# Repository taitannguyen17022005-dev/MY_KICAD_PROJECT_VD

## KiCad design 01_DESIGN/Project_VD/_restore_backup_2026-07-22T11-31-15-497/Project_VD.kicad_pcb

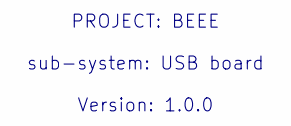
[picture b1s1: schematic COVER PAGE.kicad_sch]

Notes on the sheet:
PROJECT: BEEE sub-system: USB board Version: 1.0.0

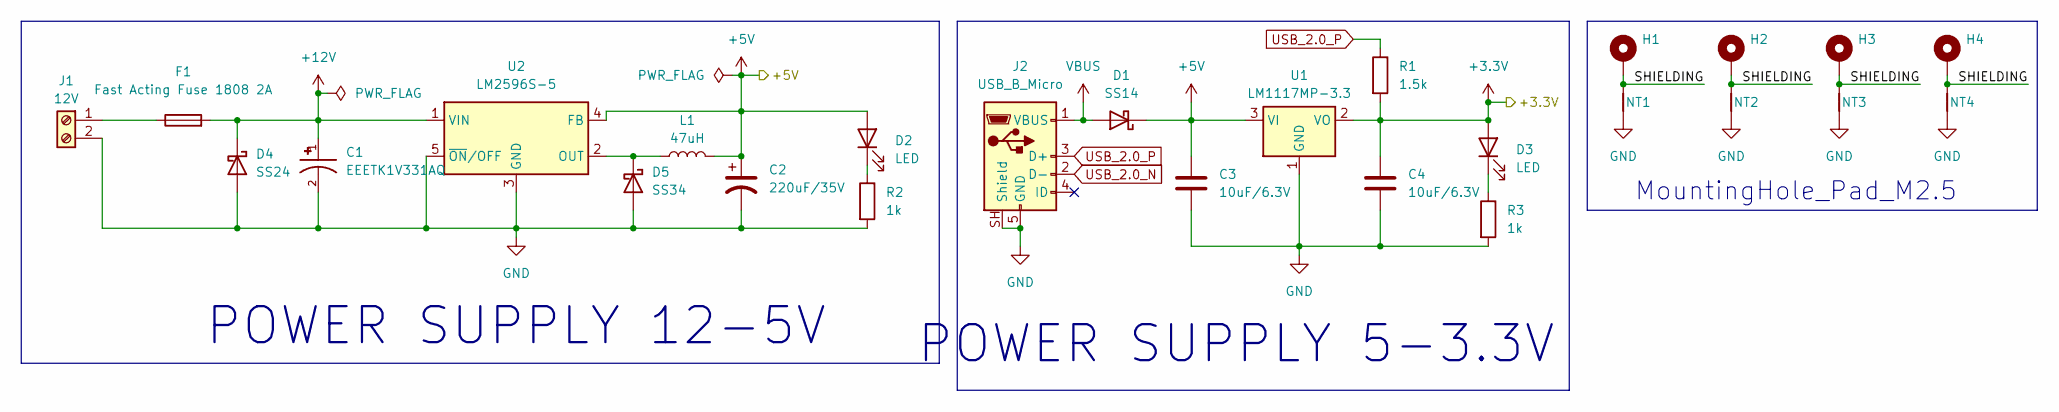
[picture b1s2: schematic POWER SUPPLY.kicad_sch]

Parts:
C1: EEETK1V331AQ; CAP_EEETK1V331AQ; PARTREV 10-Oct-19
C2: 220uF/35V; CP_Elec_8x10
C3, C4: 10uF/6.3V; C_0603_1608Metric
D1: SS14; D_SMA
D2, D3: LED; LED_0603_1608Metric
D4: SS24; D_SMA
D5: SS34; D_SMA
F1: Fast Acting Fuse 1808 2A; C_1808_4520Metric
H1, H2, H3, H4: MountingHole_Pad; MountingHole_2.7mm_M2.5_Pad
J1: 12V; TerminalBlock_Phoenix_PT-1,5-2-5.0-H_1x02_P5.00mm_Horizontal
J2: USB_B_Micro; USB_Micro-B_Molex_47346-0001
L1: 47uH; L_12x12mm_H8mm
NT1, NT2, NT3, NT4: NetTie_2; NetTie-2_SMD_Pad0.5mm
R1: 1.5k; R_0603_1608Metric
R2, R3: 1k; R_0603_1608Metric
U1: LM1117MP-3.3; SOT-223-3_TabPin2
U2: LM2596S-5; TO-263-5_TabPin3

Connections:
+3.3V: C4.1, D3.2 (A), R1.2, U1.2 (VO); also elsewhere on the board
+5V: C2.1, C3.1, D1.1 (K), D2.2 (A), L1.2, U1.3 (VI), U2.4 (FB); also elsewhere on the board
+12V: C1.1, D4.1 (K), F1.2, U2.1 (VIN)
/POWER 12 - 5V & 5 - 3.3V/SHIELDING: H1.1 (1_1), H2.1 (1_1), H3.1 (1_1), H4.1 (1_1), NT1.2, NT2.2, NT3.2, NT4.2
GND: C1.2, C2.2, C3.2, C4.2, D4.2 (A), D5.2 (A), J1.2, J2.5 (GND), J2.SH (Shield), NT1.1, NT2.1, NT3.1, NT4.1, R2.2, R3.2, U1.1 (GND), U2.3 (GND), U2.5 (~ON/OFF); also elsewhere on the board
unnamed: D2.1 (K), R2.1
unnamed: D3.1 (K), R3.1
unnamed: D5.1 (K), L1.1, U2.2 (OUT)
unnamed: F1.1, J1.1
USB_2.0_N: J2.2 (D-); also elsewhere on the board
USB_2.0_P: J2.3 (D+), R1.1; also elsewhere on the board
VBUS: D1.2 (A), J2.1 (VBUS)

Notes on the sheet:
POWER SUPPLY 12-5V
MountingHole_Pad_M2.5
POWER SUPPLY 5-3.3V

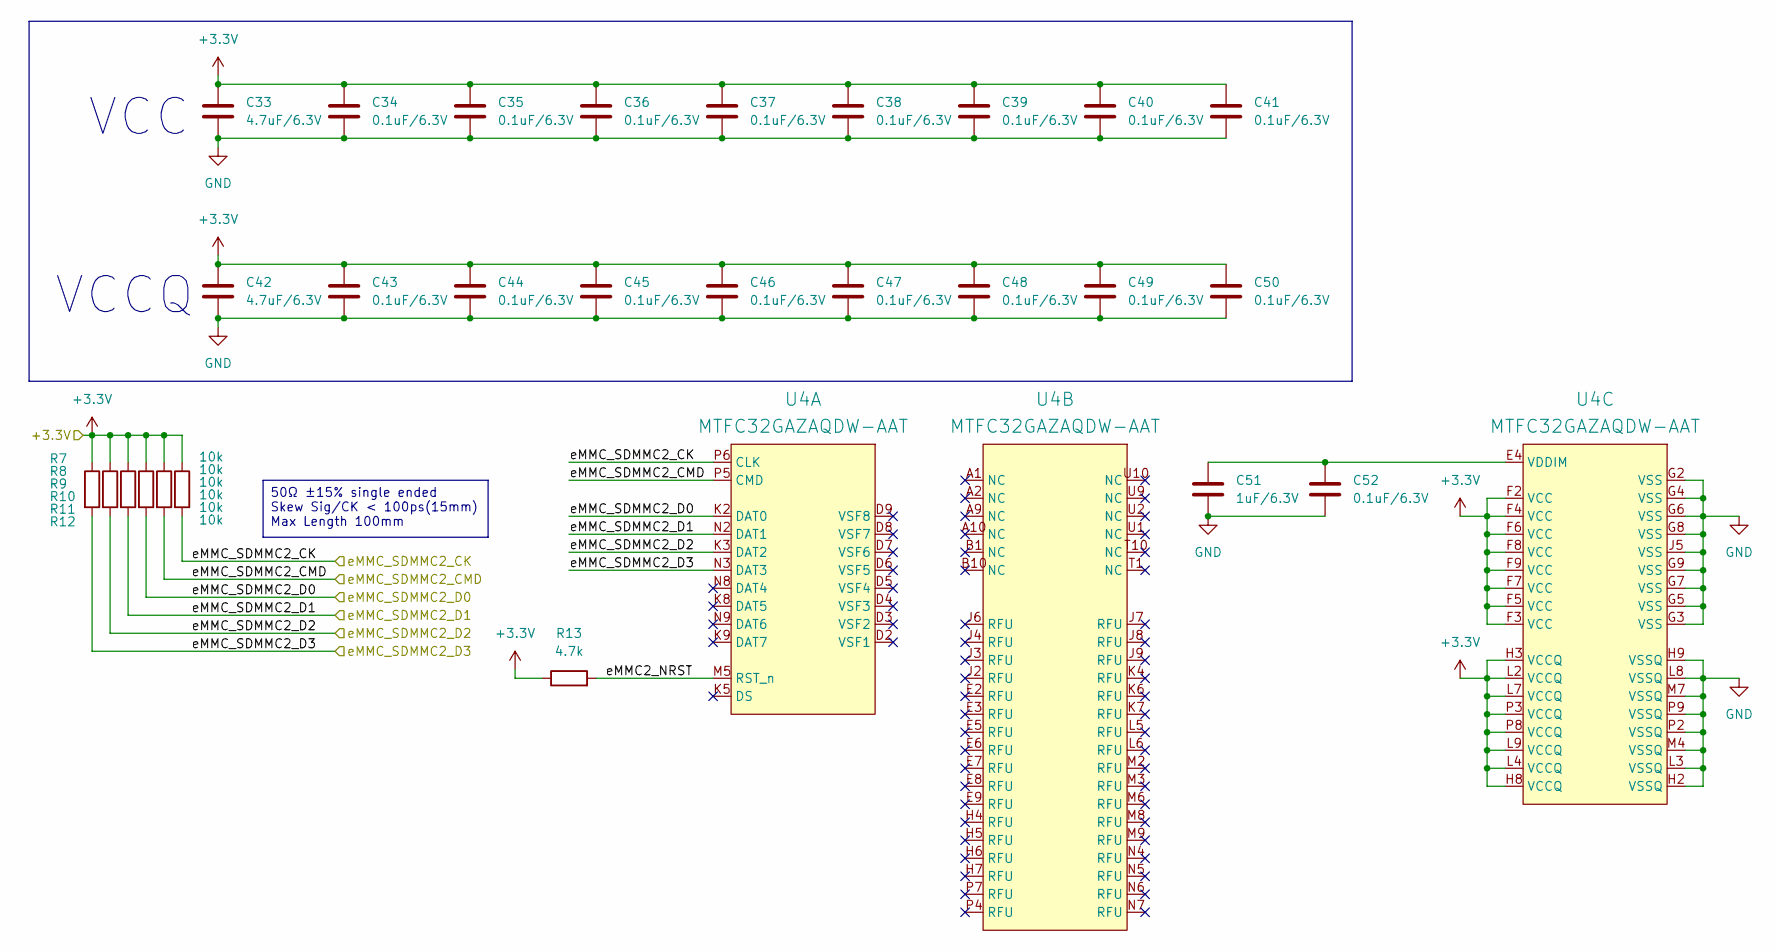
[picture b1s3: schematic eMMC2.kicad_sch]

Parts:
C33, C42: 4.7uF/6.3V; C_0603_1608Metric
C34, C35, C36, C37, C38, C39, C40, C41, C43, C44, C45, C46, C47, C48, C49, C50, C52: 0.1uF/6.3V; C_0603_1608Metric
C51: 1uF/6.3V; C_0603_1608Metric
R7, R8, R9, R10, R11, R12: 10k; C_0603_1608Metric
R13: 4.7k; C_0603_1608Metric
U4: MTFC32GAZAQDW-AAT; BGA-100_14x18mm_Layout10x17_P1mm

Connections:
+3.3V: C33.1, C34.1, C35.1, C36.1, C37.1, C38.1, C39.1, C40.1, C41.1, C42.1, C43.1, C44.1, C45.1, C46.1, C47.1, C48.1, C49.1, C50.1, R7.1, R8.1, R9.1, R10.1, R11.1, R12.1, R13.1, U4.F2 (VCC), U4.F3 (VCC), U4.F4 (VCC), U4.F5 (VCC), U4.F6 (VCC), U4.F7 (VCC), U4.F8 (VCC), U4.F9 (VCC), U4.H3 (VCCQ), U4.H8 (VCCQ), U4.L2 (VCCQ), U4.L4 (VCCQ), U4.L7 (VCCQ), U4.L9 (VCCQ), U4.P3 (VCCQ), U4.P8 (VCCQ); also elsewhere on the board
/eMMC2/eMMC2_NRST: R13.2, U4.M5 (RST_n)
/eMMC2/eMMC_SDMMC2_CK: R12.2, U4.P6 (CLK); also elsewhere on the board
/eMMC2/eMMC_SDMMC2_CMD: R11.2, U4.P5 (CMD); also elsewhere on the board
/eMMC2/eMMC_SDMMC2_D0: R10.2, U4.K2 (DAT0); also elsewhere on the board
/eMMC2/eMMC_SDMMC2_D1: R9.2, U4.N2 (DAT1); also elsewhere on the board
/eMMC2/eMMC_SDMMC2_D2: R8.2, U4.K3 (DAT2); also elsewhere on the board
/eMMC2/eMMC_SDMMC2_D3: R7.2, U4.N3 (DAT3); also elsewhere on the board
GND: C33.2, C34.2, C35.2, C36.2, C37.2, C38.2, C39.2, C40.2, C41.2, C42.2, C43.2, C44.2, C45.2, C46.2, C47.2, C48.2, C49.2, C50.2, C51.2, C52.2, U4.G2 (VSS), U4.G3 (VSS), U4.G4 (VSS), U4.G5 (VSS), U4.G6 (VSS), U4.G7 (VSS), U4.G8 (VSS), U4.G9 (VSS), U4.H2 (VSSQ), U4.H9 (VSSQ), U4.J5 (VSS), U4.L3 (VSSQ), U4.L8 (VSSQ), U4.M4 (VSSQ), U4.M7 (VSSQ), U4.P2 (VSSQ), U4.P9 (VSSQ); also elsewhere on the board
unnamed: C51.1, C52.1, U4.E4 (VDDIM)

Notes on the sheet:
VCC
VCCQ
50Ω ±15% single ended Skew Sig/CK < 100ps(15mm) Max Length 100mm

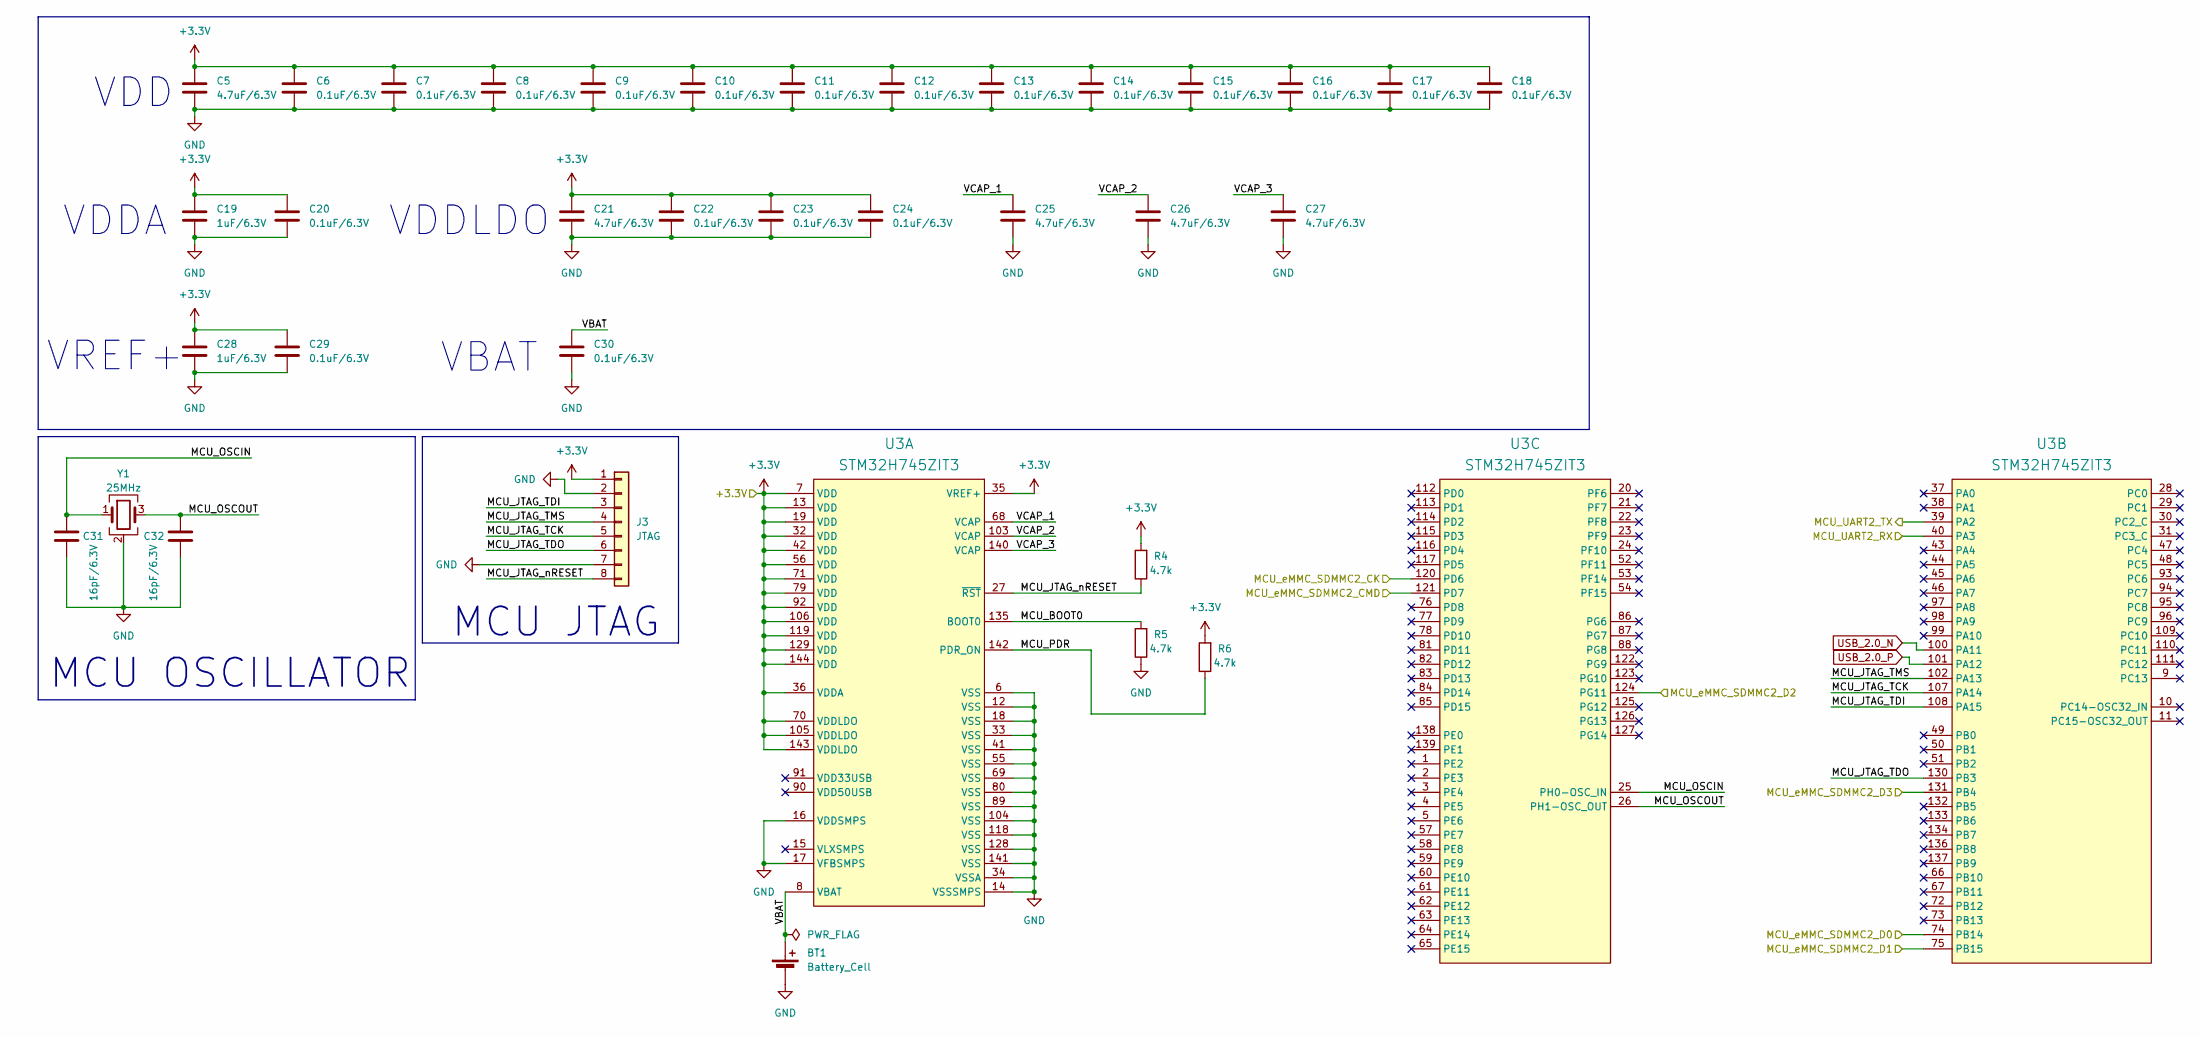
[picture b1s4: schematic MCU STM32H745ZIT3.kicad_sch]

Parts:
BT1: Battery_Cell; BatteryHolder_Keystone_1060_1x2032
C5, C21, C25, C26, C27: 4.7uF/6.3V; C_0603_1608Metric
C6, C7, C8, C9, C10, C11, C12, C13, C14, C15, C16, C17, C18, C20, C22, C23, C24, C29, C30: 0.1uF/6.3V; C_0603_1608Metric
C19, C28: 1uF/6.3V; C_0603_1608Metric
C31, C32: 16pF/6.3V; C_0603_1608Metric
J3: JTAG; PinHeader_1x08_P2.54mm_Vertical
R4, R5, R6: 4.7k; C_0603_1608Metric
U3: STM32H745ZIT3; LQFP-144_20x20mm_P0.5mm; Manufacturer Part Number STM32H745ZIT6; Digikey Description HIGH-PERFORMANCE AND DSP WITH DP
Y1: 25MHz; Crystal_SMD_3225-4Pin_3.2x2.5mm

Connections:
+3.3V: C5.1, C6.1, C7.1, C8.1, C9.1, C10.1, C11.1, C12.1, C13.1, C14.1, C15.1, C16.1, C17.1, C18.1, C19.1, C20.1, C21.1, C22.1, C23.1, C24.1, C28.1, C29.1, J3.1, R4.2, R6.2, U3.7 (VDD), U3.13 (VDD), U3.19 (VDD), U3.32 (VDD), U3.35 (VREF+), U3.36 (VDDA), U3.42 (VDD), U3.56 (VDD), U3.70 (VDDLDO), U3.71 (VDD), U3.79 (VDD), U3.92 (VDD), U3.105 (VDDLDO), U3.106 (VDD), U3.119 (VDD), U3.129 (VDD), U3.143 (VDDLDO), U3.144 (VDD); also elsewhere on the board
/ISO_UART/ISO_UART2_RX: U3.40 (PA3); also elsewhere on the board
/ISO_UART/ISO_UART2_TX: U3.39 (PA2); also elsewhere on the board
/MCU STM32H745ZIT3/MCU_BOOT0: R5.2, U3.135 (BOOT0)
/MCU STM32H745ZIT3/MCU_JTAG_TCK: J3.5, U3.107 (PA14)
/MCU STM32H745ZIT3/MCU_JTAG_TDI: J3.3, U3.108 (PA15)
/MCU STM32H745ZIT3/MCU_JTAG_TDO: J3.6, U3.130 (PB3)
/MCU STM32H745ZIT3/MCU_JTAG_TMS: J3.4, U3.102 (PA13)
/MCU STM32H745ZIT3/MCU_JTAG_nRESET: J3.8, R4.1, U3.27 (~RST)
/MCU STM32H745ZIT3/MCU_OSCIN: C31.1, U3.25 (PH0-OSC_IN), Y1.1
/MCU STM32H745ZIT3/MCU_OSCOUT: C32.1, U3.26 (PH1-OSC_OUT), Y1.3
/MCU STM32H745ZIT3/MCU_PDR: R6.1, U3.142 (PDR_ON)
/MCU STM32H745ZIT3/VBAT: BT1.1 (+), C30.1, U3.8 (VBAT)
/MCU STM32H745ZIT3/VCAP_1: C25.1, U3.68 (VCAP)
/MCU STM32H745ZIT3/VCAP_2: C26.1, U3.103 (VCAP)
/MCU STM32H745ZIT3/VCAP_3: C27.1, U3.140 (VCAP)
/eMMC2/eMMC_SDMMC2_CK: U3.120 (PD6); also elsewhere on the board
/eMMC2/eMMC_SDMMC2_CMD: U3.121 (PD7); also elsewhere on the board
/eMMC2/eMMC_SDMMC2_D0: U3.74 (PB14); also elsewhere on the board
/eMMC2/eMMC_SDMMC2_D1: U3.75 (PB15); also elsewhere on the board
/eMMC2/eMMC_SDMMC2_D2: U3.124 (PG11); also elsewhere on the board
/eMMC2/eMMC_SDMMC2_D3: U3.131 (PB4); also elsewhere on the board
GND: BT1.2 (-), C5.2, C6.2, C7.2, C8.2, C9.2, C10.2, C11.2, C12.2, C13.2, C14.2, C15.2, C16.2, C17.2, C18.2, C19.2, C20.2, C21.2, C22.2, C23.2, C24.2, C25.2, C26.2, C27.2, C28.2, C29.2, C30.2, C31.2, C32.2, J3.2, J3.7, R5.1, U3.6 (VSS), U3.12 (VSS), U3.14 (VSSSMPS), U3.16 (VDDSMPS), U3.17 (VFBSMPS), U3.18 (VSS), U3.33 (VSS), U3.34 (VSSA), U3.41 (VSS), U3.55 (VSS), U3.69 (VSS), U3.80 (VSS), U3.89 (VSS), U3.104 (VSS), U3.118 (VSS), U3.128 (VSS), U3.141 (VSS), Y1.2 (G), Y1.4 (G); also elsewhere on the board
USB_2.0_N: U3.100 (PA11); also elsewhere on the board
USB_2.0_P: U3.101 (PA12); also elsewhere on the board

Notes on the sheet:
VDD
MCU JTAG
VREF+
MCU OSCILLATOR
VBAT
VDDLDO
VDDA

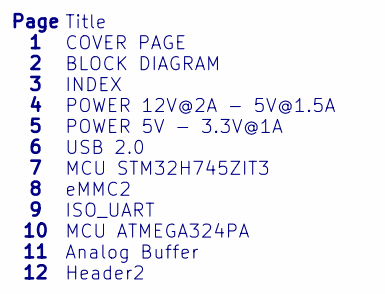
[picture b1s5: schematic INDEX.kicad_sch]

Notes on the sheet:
Page 1 2 3 4 5 6 7 8 9 10 11 12
Title COVER PAGE BLOCK DIAGRAM INDEX POWER 12V@2A - 5V@1.5A POWER 5V - 3.3V@1A USB 2.0 MCU STM32H745ZIT3 eMMC2 ISO_UART MCU ATMEGA324PA Analog Buffer Header2

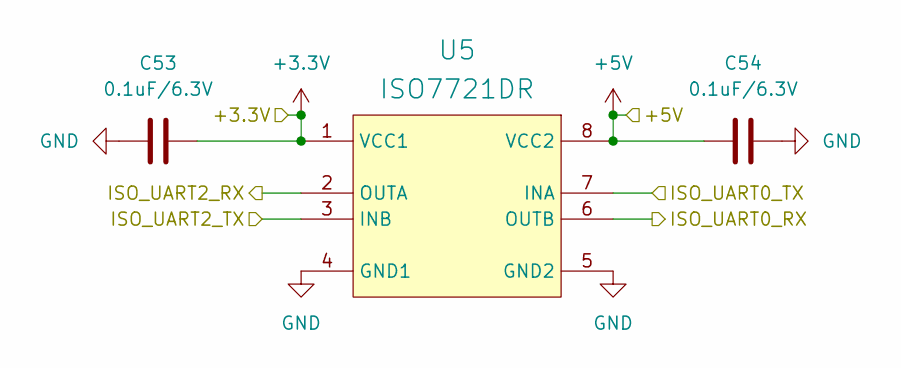
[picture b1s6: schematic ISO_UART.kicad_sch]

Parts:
C53, C54: 0.1uF/6.3V; C_0603_1608Metric
U5: ISO7721DR; SOIC-8_3.9x4.9mm_P1.27mm

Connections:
+3.3V: C53.2, U5.1 (VCC1); also elsewhere on the board
+5V: C54.2, U5.8 (VCC2); also elsewhere on the board
/ISO_UART/ISO_UART0_RX: U5.6 (OUTB); also elsewhere on the board
/ISO_UART/ISO_UART0_TX: U5.7 (INA); also elsewhere on the board
/ISO_UART/ISO_UART2_RX: U5.2 (OUTA); also elsewhere on the board
/ISO_UART/ISO_UART2_TX: U5.3 (INB); also elsewhere on the board
GND: C53.1, C54.1, U5.4 (GND1), U5.5 (GND2); also elsewhere on the board

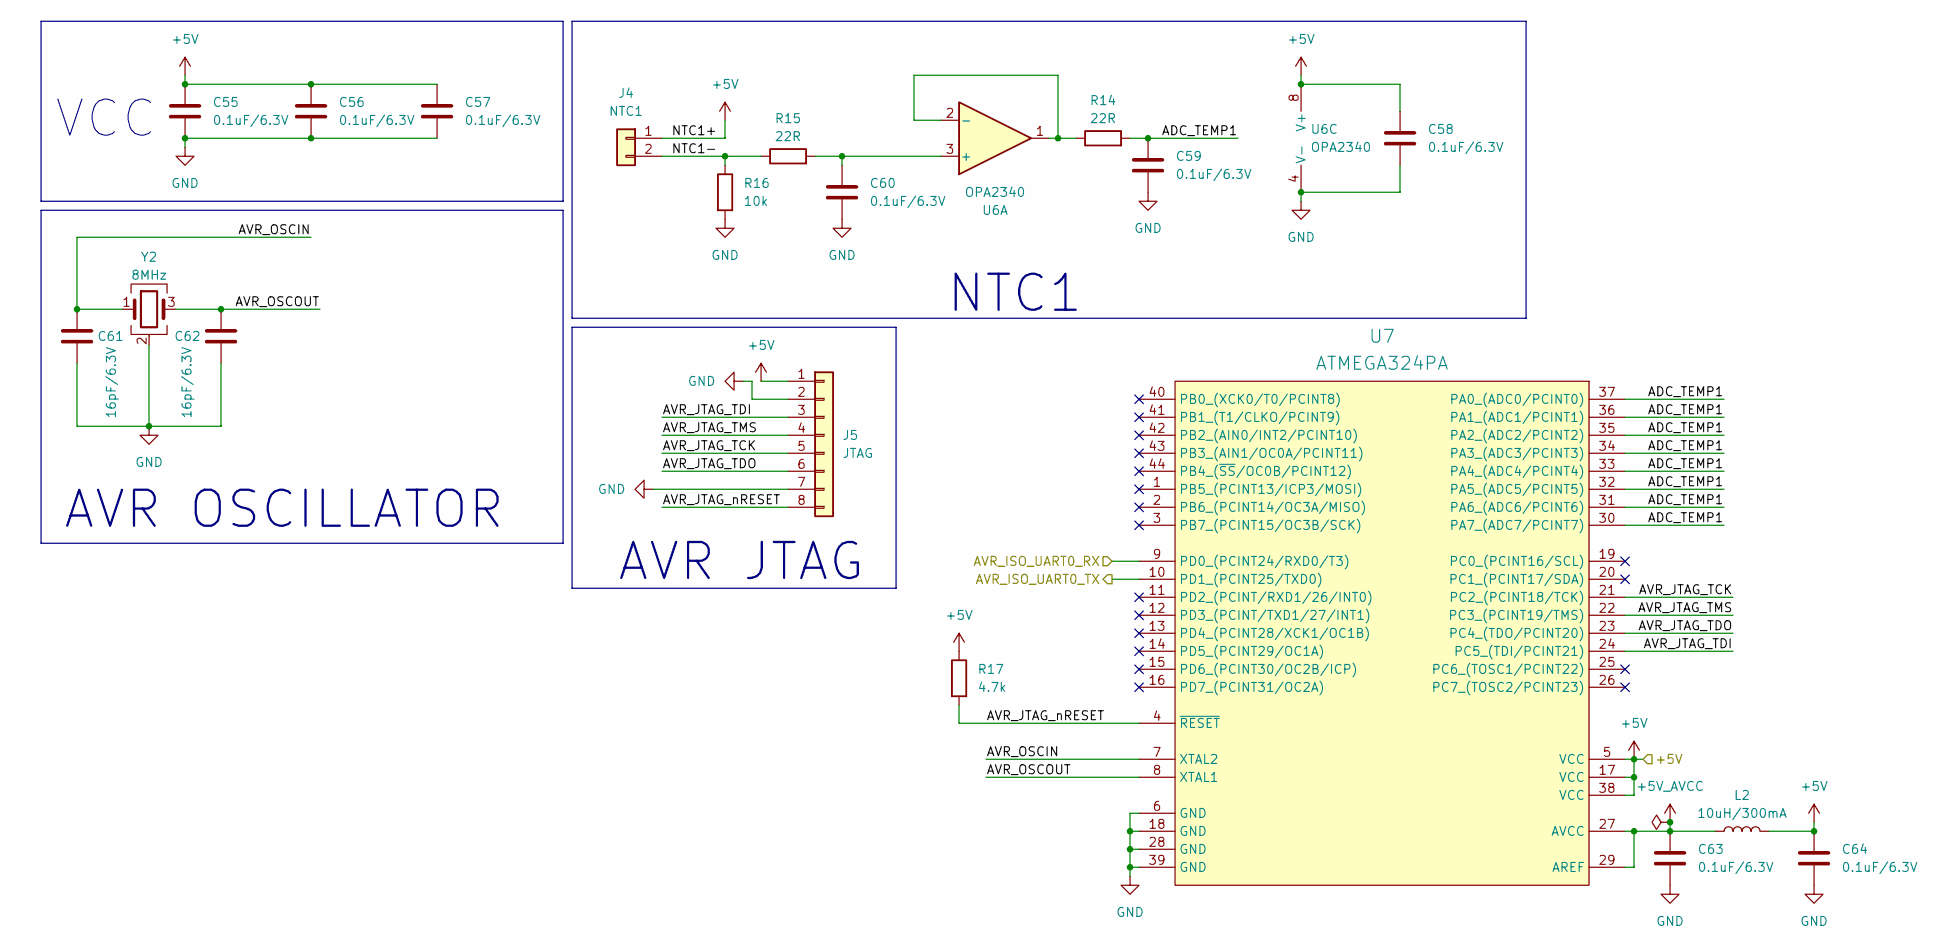
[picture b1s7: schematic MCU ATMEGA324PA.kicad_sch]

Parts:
C55, C56, C57, C58, C59, C60, C63, C64: 0.1uF/6.3V; C_0603_1608Metric
C61, C62: 16pF/6.3V; C_0603_1608Metric
J4: NTC1; PinHeader_1x02_P2.54mm_Vertical
J5: JTAG; PinHeader_1x08_P2.54mm_Vertical
L2: 10uH/300mA; L_0805_2012Metric
R14, R15: 22R; C_0603_1608Metric
R16: 10k; C_0603_1608Metric
R17: 4.7k; C_0603_1608Metric
U6: OPA2340; SOIC-8_3.9x4.9mm_P1.27mm
U7: ATMEGA324PA; TQFP-44_10x10mm_P0.8mm; Manufacturer Part Number ATMEGA324PA-AU
Y2: 8MHz; Crystal_SMD_3225-4Pin_3.2x2.5mm

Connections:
+5V: C55.1, C56.1, C57.1, C58.1, C64.1, J4.1, J5.1, L2.2, R17.1, U6.8 (V+), U7.5 (VCC), U7.17 (VCC), U7.38 (VCC); also elsewhere on the board
+5V_AVCC: C63.1, L2.1, U7.27 (AVCC), U7.29 (AREF)
/ISO_UART/ISO_UART0_RX: U7.9 (PD0_(PCINT24/RXD0/T3)); also elsewhere on the board
/ISO_UART/ISO_UART0_TX: U7.10 (PD1_(PCINT25/TXD0)); also elsewhere on the board
/MCU ATMEGA324PA/ADC_TEMP1: C59.1, R14.2, U7.30 (PA7_(ADC7/PCINT7)), U7.31 (PA6_(ADC6/PCINT6)), U7.32 (PA5_(ADC5/PCINT5)), U7.33 (PA4_(ADC4/PCINT4)), U7.34 (PA3_(ADC3/PCINT3)), U7.35 (PA2_(ADC2/PCINT2)), U7.36 (PA1_(ADC1/PCINT1)), U7.37 (PA0_(ADC0/PCINT0))
/MCU ATMEGA324PA/AVR_JTAG_TCK: J5.5, U7.21 (PC2_(PCINT18/TCK))
/MCU ATMEGA324PA/AVR_JTAG_TDI: J5.3, U7.24 (PC5_(TDI/PCINT21))
/MCU ATMEGA324PA/AVR_JTAG_TDO: J5.6, U7.23 (PC4_(TDO/PCINT20))
/MCU ATMEGA324PA/AVR_JTAG_TMS: J5.4, U7.22 (PC3_(PCINT19/TMS))
/MCU ATMEGA324PA/AVR_JTAG_nRESET: J5.8, R17.2, U7.4 (~RESET)
/MCU ATMEGA324PA/AVR_OSCIN: C61.1, U7.7 (XTAL2), Y2.1
/MCU ATMEGA324PA/AVR_OSCOUT: C62.1, U7.8 (XTAL1), Y2.3
/MCU ATMEGA324PA/NTC1-: J4.2, R15.1, R16.1
GND: C55.2, C56.2, C57.2, C58.2, C59.2, C60.2, C61.2, C62.2, C63.2, C64.2, J5.2, J5.7, R16.2, U6.4 (V-), U7.6 (GND), U7.18 (GND), U7.28 (GND), U7.39 (GND), Y2.2 (G), Y2.4 (G); also elsewhere on the board
unnamed: C60.1, R15.2, U6.3 (+)
unnamed: R14.1, U6.1, U6.2 (-)

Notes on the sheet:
AVR OSCILLATOR
VCC
AVR JTAG
NTC1

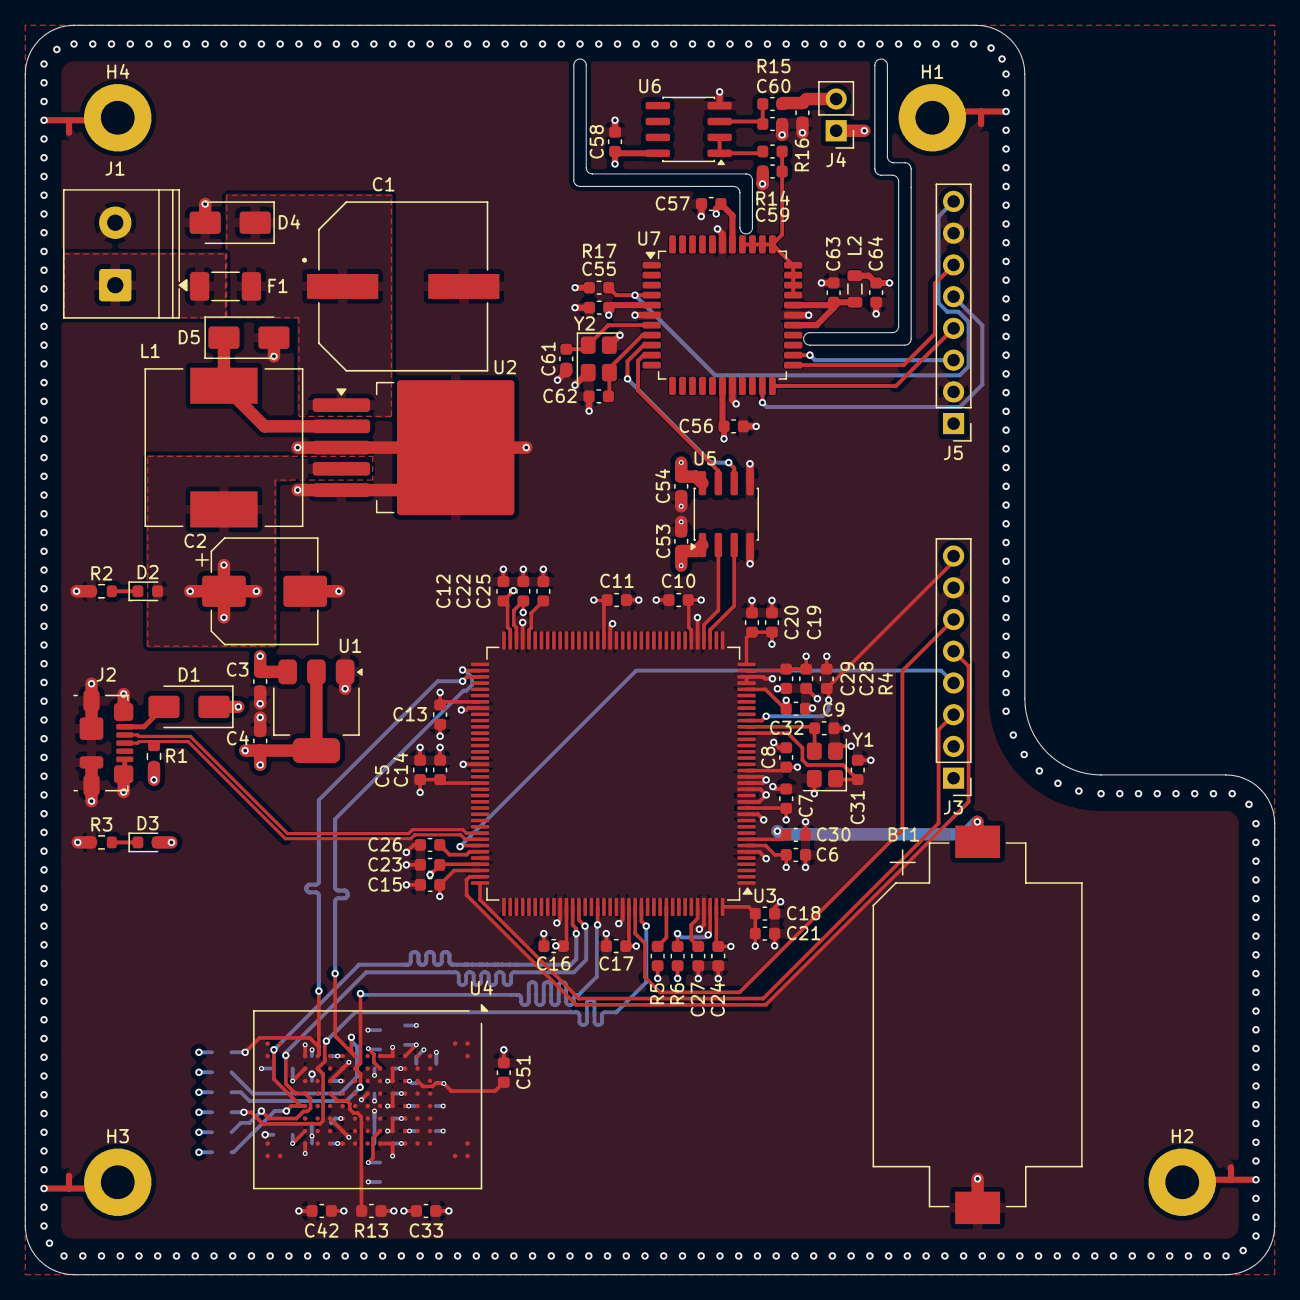
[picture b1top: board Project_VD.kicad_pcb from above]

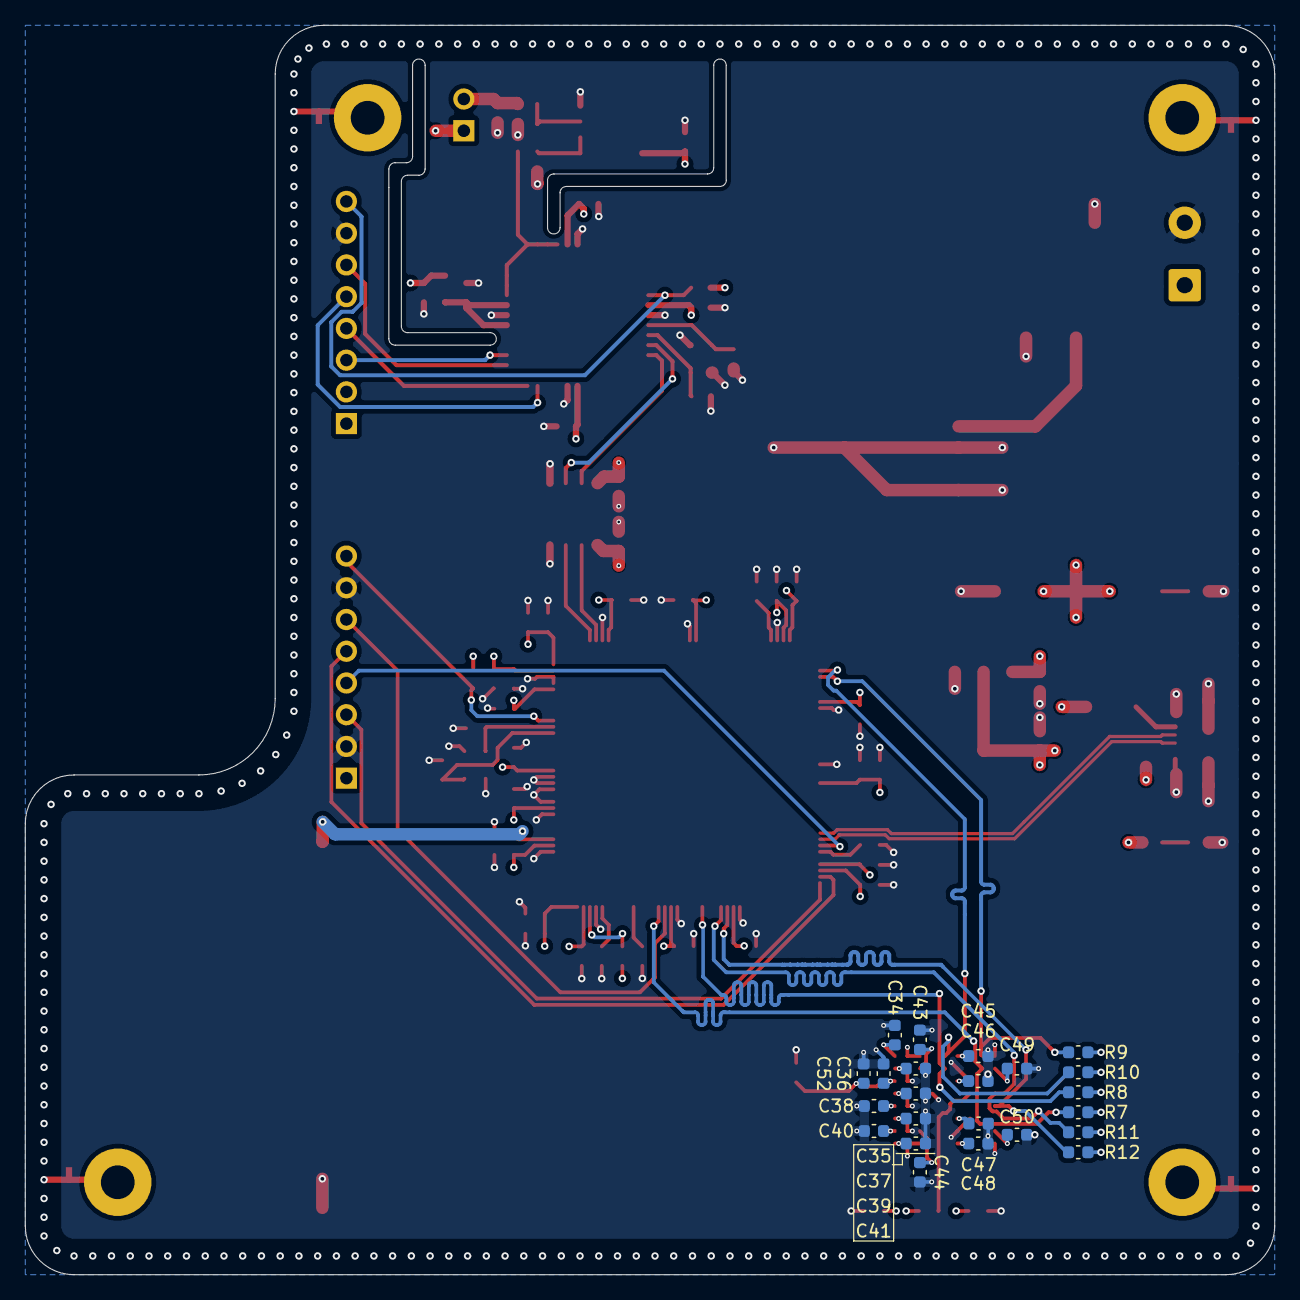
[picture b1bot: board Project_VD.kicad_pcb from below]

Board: 4 copper layers, 100.0 x 100.0 mm, 112 parts (23 on the bottom side), 49 nets.

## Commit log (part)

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2026-06-20 Chore: Khoi tao cau truc thu muc chuan va file.gitignore
2026-06-20 update 20/06/2026
2026-06-21 update 21/06/2026
2026-06-25 update Layout PCB
2026-06-25 update 26/06/2026
